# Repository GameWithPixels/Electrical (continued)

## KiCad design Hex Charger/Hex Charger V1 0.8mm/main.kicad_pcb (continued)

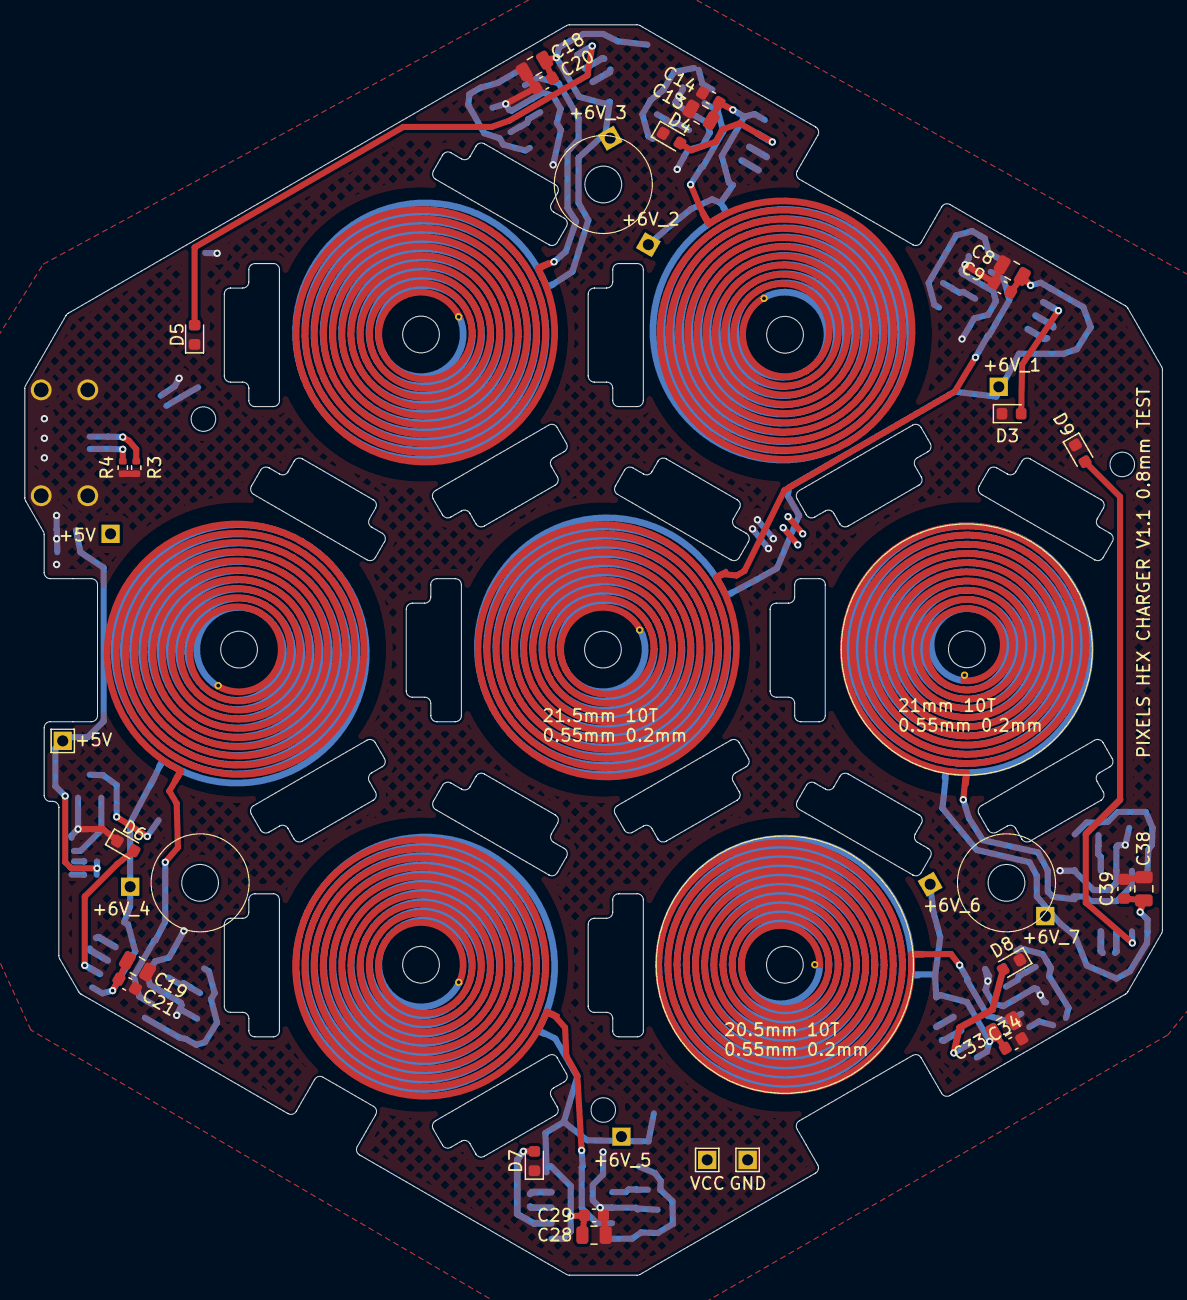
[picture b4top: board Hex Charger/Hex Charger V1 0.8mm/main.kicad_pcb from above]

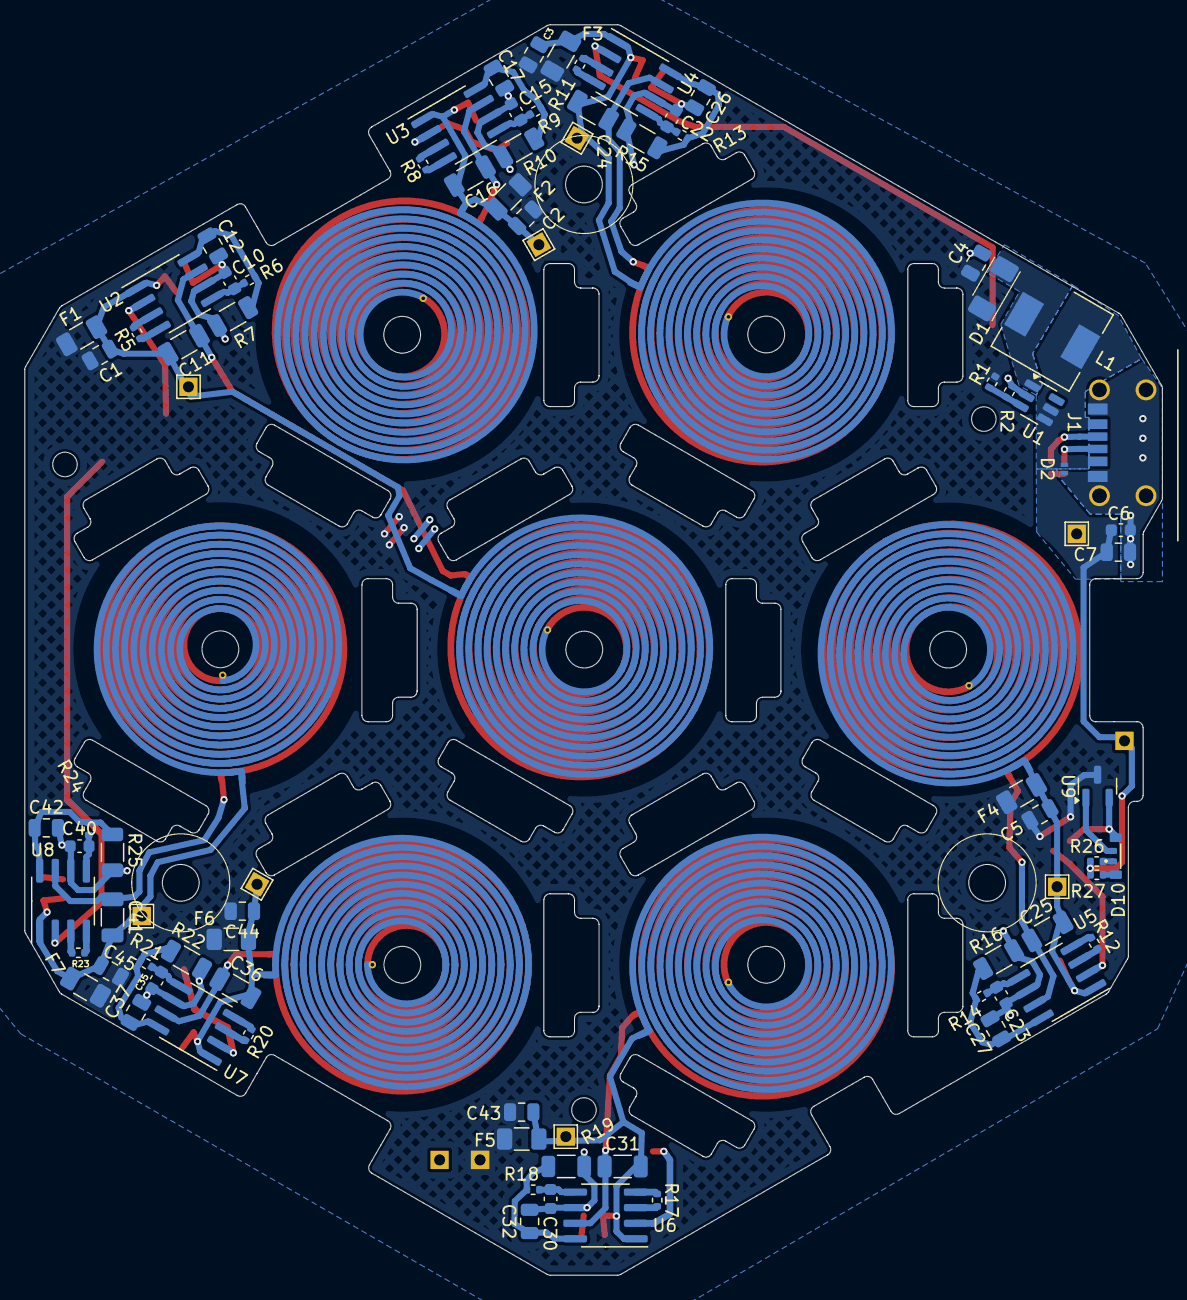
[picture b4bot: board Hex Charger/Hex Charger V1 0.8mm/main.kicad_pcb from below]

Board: 2 copper layers, 92.9 x 102.1 mm, 118 parts (85 on the bottom side), 59 nets.

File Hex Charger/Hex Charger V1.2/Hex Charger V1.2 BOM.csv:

"Reference","Value","Datasheet","Footprint","Qty","DNP","Manufacturer","Part Number","LCSC Part #"
"C1,C2,C3,C5,C12,C17,C26,C27,C32,C37,C42,C43,C44,C45","10uF 50V 10% X5R","~","Capacitor_SMD:C_0805_2012Metric","14","","Murata","GRM21BR61H106KE43L","C440198"
"C4,C7,C8,C13,C18,C19,C28,C33,C38","22uF 25V 20% X5R","~","Capacitor_SMD:C_0805_2012Metric","9","","Murata","GRM21BR61E226ME44L","C86816"
"C6,C9,C10,C14,C15,C20,C21,C22,C23,C29,C30,C34,C35,C39,C40","0.1uF 16V 10% X7R","~","Capacitor_SMD:C_0603_1608Metric","15","","Samsung Electro-Mechanics","CL10B104KO8NNNC","C66501"
"C11,C16,C24,C25,C31,C36,C41","33nF 50V COG","~","Capacitor_SMD:C_1206_3216Metric","7","","Murata","GRM3195C1H333JA01D","C97930"
"C46,C47,C48,C49,C50,C51,C52","100uF 10V 20%","~","Capacitor_SMD:CP_Elec_4x5.4","7","","ROQANG","CK1A470M-CRC54","C3001223"
"D1","D","~","Pixels-dice:SMAF","1","","GOODWORK","SS54F","C908671"
"D2","D_TVS","~","Pixels-dice:DFN","1","","Murata","LXES1UTAA1-157","C5210979"
"D3,D4,D5,D6,D7,D8,D9","LED","~","LED_SMD:LED_0603_1608Metric","7","","Lite-On","LTST-C191KRKT","C125099"
"D10","LED_Dual_KKAA","~","Pixels-dice:XL-3210SURUGC","1","","XINGLIGHT","XL-3210SURUGC","C965883"
"F1,F2,F3,F4,F5,F6,F7","250mA 150mR","~","Fuse:Fuse_1206_3216Metric","7","","BHFUSE","BSMD1206-025-33V","C2977524"
"J1","USB_C_Receptacle_USB2.0","https://www.usb.org/sites/default/files/documents/usb_type-c.zip","Pixels-dice:USB-C-SMD_10P-P1.00-L6.8-W8.9","1","","Korean Hroparts Elec","TYPE-C-31-M-17","C283540"
"J2,J3,J4,J5,J6,J7,J8","Conn_01x02_Socket","~","Pixels-dice:PCB Coil 25_11_0.8_0.2","7","DNP","","",""
"L1","10uH 500mA","~","Inductor_SMD:L_Wuerth_HCM-7050","1","","Ruishen","RS0650-100MS","C32712977"
"R1","470k","~","Resistor_SMD:R_0402_1005Metric","1","","UNI-ROYAL(Uniroyal Elec)","0402WGF4703TCE","C25790"
"R2","52.3k","~","Resistor_SMD:R_0402_1005Metric","1","","UNI-ROYAL(Uniroyal Elec)","0402WGF5232TCE","C26982"
"R3,R4","5.1k 1%","~","Resistor_SMD:R_0402_1005Metric","2","","UNI-ROYAL(Uniroyal Elec)","0402WGF5101TCE","C25905"
"R5,R8,R11,R12,R17,R20,R23","120K 1%","~","Resistor_SMD:R_0402_1005Metric","7","","UNI-ROYAL(Uniroyal Elec)","0402WGF1203TCE","C25750"
"R6,R9,R13,R14,R18,R21,R24","1k 1%","~","Resistor_SMD:R_0402_1005Metric","7","","UNI-ROYAL(Uniroyal Elec)","0402WGF1001TCE","C11702"
"R7,R10,R15,R16,R19,R22,R25","0.91R","~","Resistor_SMD:R_1206_3216Metric","7","","YAGEO","RL1206FR-7W0R91L","C136987"
"R26,R27","200R 5%","~","Resistor_SMD:R_0402_1005Metric","2","","UNI-ROYAL(Uniroyal Elec)","0402WGF2000TCE","C25087"
"U1","MT3608B","https://www.olimex.com/Products/Breadboarding/BB-PWR-3608/re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","Package_TO_SOT_SMD:SOT-23-6","1","","XI'AN Aerosemi Tech","MT3608B","C19189893"
"U2,U3,U4,U5,U6,U7,U8","XKT520","","Pixels-dice:SOIC-8_3.9x4.9mm_P1.27mm","7","","XKT","520",""
"U9","SSP61CN4802MR","","Package_TO_SOT_SMD:SOT-23","1","","UMW(Youtai Semiconductor Co., Ltd.)","HT7050S","C2842953"
"W1","VBUS","","Pixels-dice:TestPoint_1.5x1.5_Drill0.9mm","1","","","",""
"W2","GND","","Pixels-dice:TestPoint_1.5x1.5_Drill0.9mm","1","","","",""
"W3","5V","","Pixels-dice:TestPoint_1.5x1.5_Drill0.9mm","1","","","",""
"W4","VCC","","Pixels-dice:TestPoint_1.5x1.5_Drill0.9mm","1","","","",""
"W5,W6,W7,W8,W9,W10,W11","+6V","","Pixels-dice:TestPoint_1.5x1.5_Drill0.9mm","7","","","",""
